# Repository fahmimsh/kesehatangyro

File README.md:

# kesehatangyro
https://github.com/firebitlab/arduino/tree/master/MPU2/lib

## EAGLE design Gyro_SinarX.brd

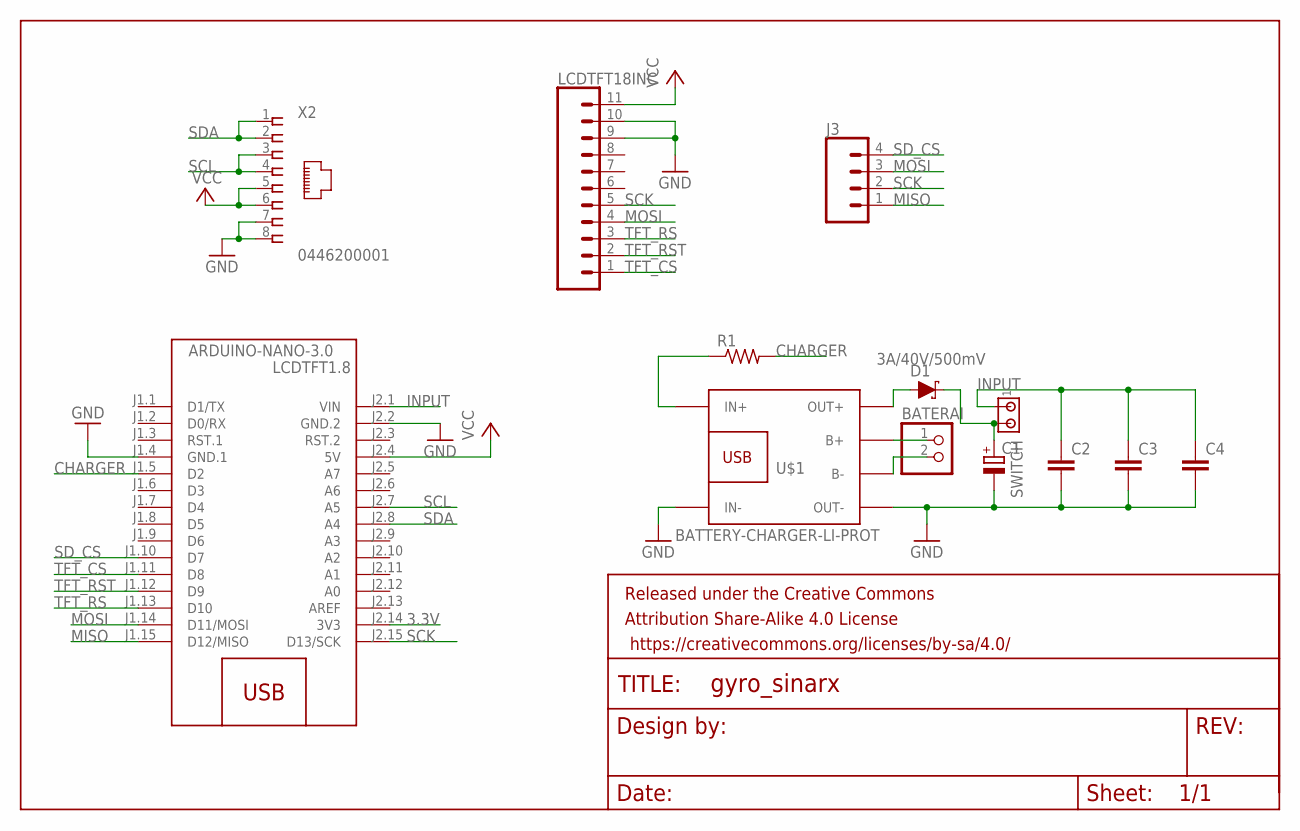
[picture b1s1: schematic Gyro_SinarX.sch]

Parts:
BATERAI: PINHD-1X2/90; 1X02/90
C1: CPOL-EUE2.5-7; E2,5-7
C2, C3, C4: C-EUC0805K; C0805K
D1: 3A/40V/500mV; SMA-DIODE
FRAME1: FRAME-LEDGER; CREATIVE_COMMONS
J3: CONN_04PTH; 1X04
LCDTFT1.8: ARDUINO-NANO-3.0
LCDTFT18INC: CONN_11; 1X11
R1: R-US_0207/10; 0207/10
SWITCH: MTA02-100; 10X02MTA
U$1: BATTERY-CHARGER-LI-PROT
X2: 0446200001

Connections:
3.3V: LCDTFT1.8.J2.14 (3V3)
CHARGER: LCDTFT1.8.J1.5 (D2), R1.2
GND: C1.-, C2.2, C3.2, C4.2, LCDTFT1.8.J1.4 (GND.1), LCDTFT1.8.J2.2 (GND.2), LCDTFT18INC.9, LCDTFT18INC.10, U$1.IN-, U$1.OUT-, X2.7, X2.8
INPUT: C2.1, C3.1, C4.1, LCDTFT1.8.J2.1 (VIN), SWITCH.1
MISO: J3.1, LCDTFT1.8.J1.15 (D12/MISO)
MOSI: J3.3, LCDTFT1.8.J1.14 (D11/MOSI), LCDTFT18INC.4
unnamed: D1.A, U$1.OUT+
unnamed: R1.1, U$1.IN+
unnamed: C1.+, D1.C, SWITCH.2
unnamed: BATERAI.1, U$1.B+
unnamed: BATERAI.2, U$1.B-
SCK: J3.2, LCDTFT1.8.J2.15 (D13/SCK), LCDTFT18INC.5
SCL: LCDTFT1.8.J2.7 (A5), X2.3, X2.4
SDA: LCDTFT1.8.J2.8 (A4), X2.1, X2.2
SD_CS: J3.4, LCDTFT1.8.J1.10 (D7)
TFT_CS: LCDTFT1.8.J1.11 (D8), LCDTFT18INC.1
TFT_RS: LCDTFT1.8.J1.13 (D10), LCDTFT18INC.3
TFT_RST: LCDTFT1.8.J1.12 (D9), LCDTFT18INC.2
VCC: LCDTFT1.8.J2.4 (5V), LCDTFT18INC.11, X2.5, X2.6

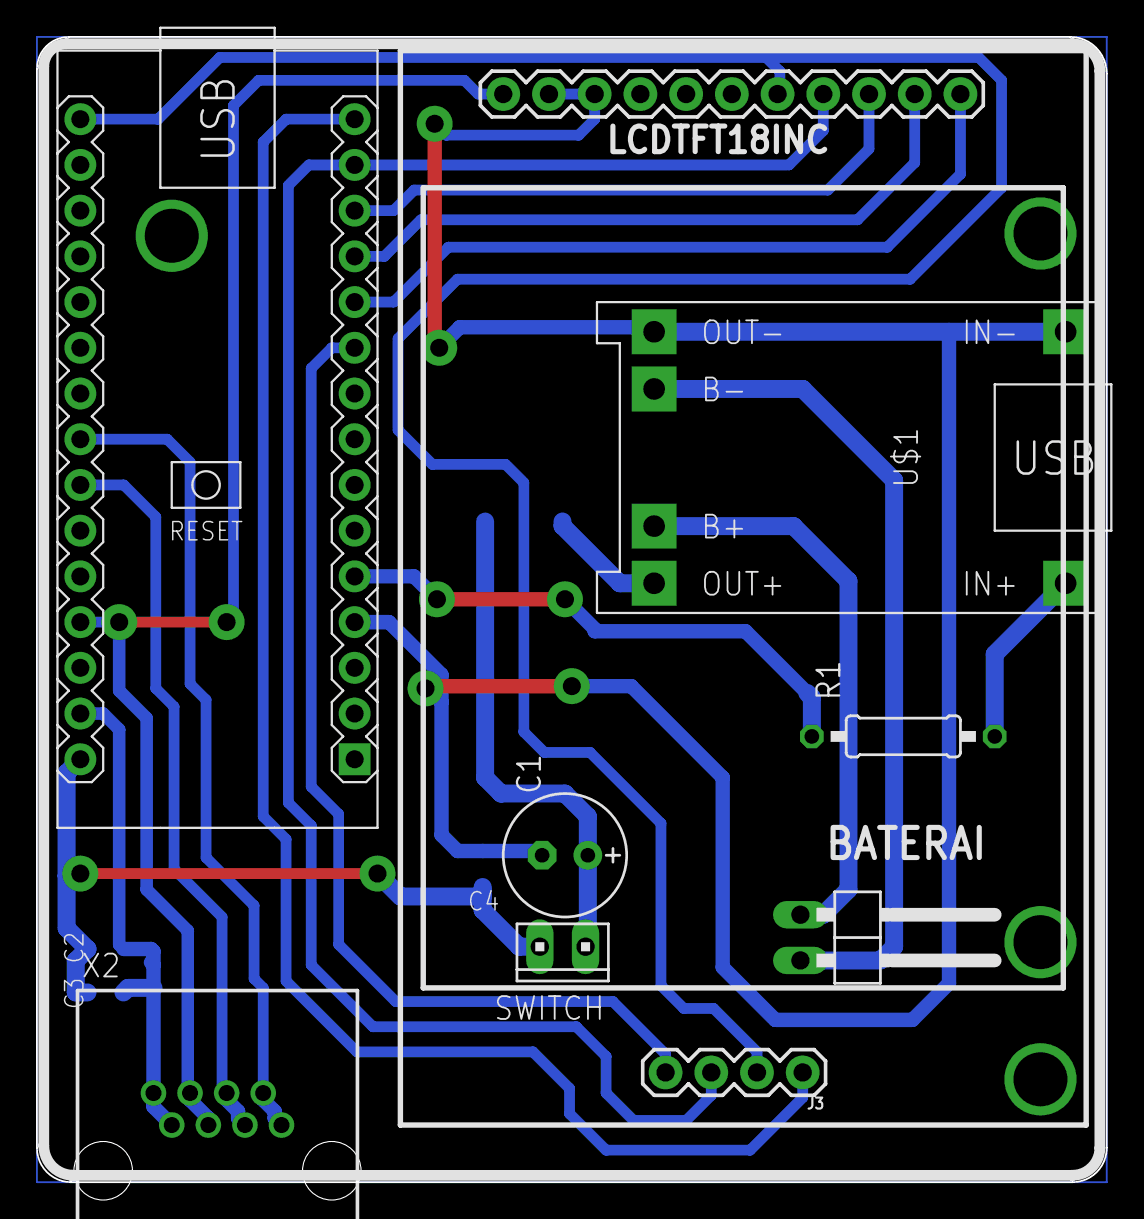
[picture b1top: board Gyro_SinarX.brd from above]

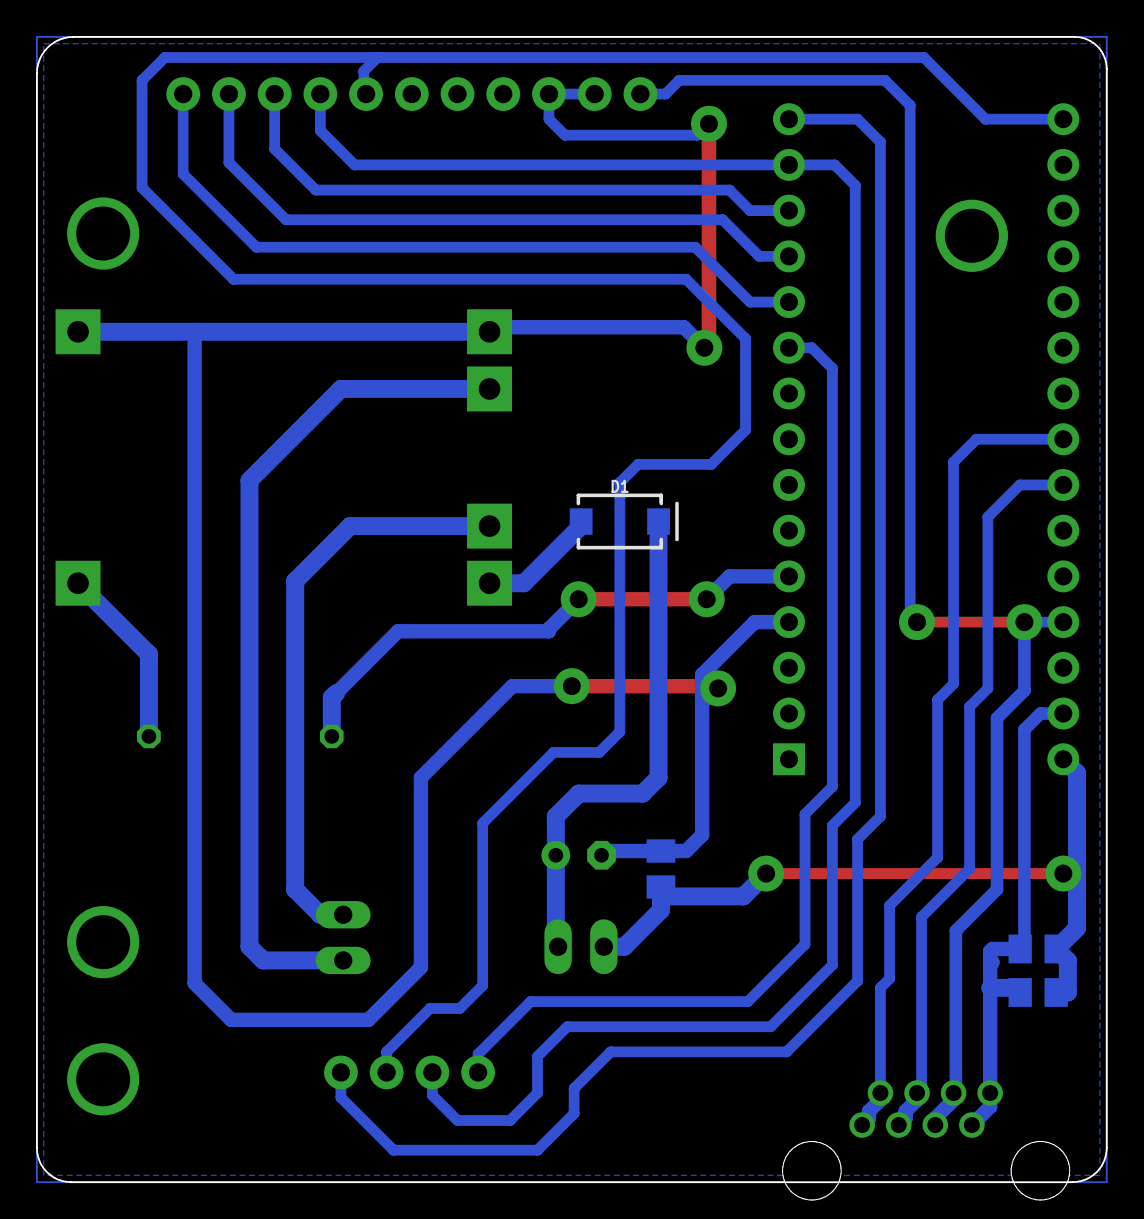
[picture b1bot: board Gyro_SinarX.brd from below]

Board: 2 copper layers, 59.4 x 63.6 mm, 14 parts (4 on the bottom side), 18 nets.

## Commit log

2021-09-12 upfate

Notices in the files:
parts and their libraries:
diy-modules: Released under the Creative Commons Attribution 4.0 International License: http://creativecommons.org/licenses/by/4.0
SparkFun-Connectors: Licensing: Creative Commons ShareAlike 4.0 International - https://creativecommons.org/licenses/by-sa/4.0
